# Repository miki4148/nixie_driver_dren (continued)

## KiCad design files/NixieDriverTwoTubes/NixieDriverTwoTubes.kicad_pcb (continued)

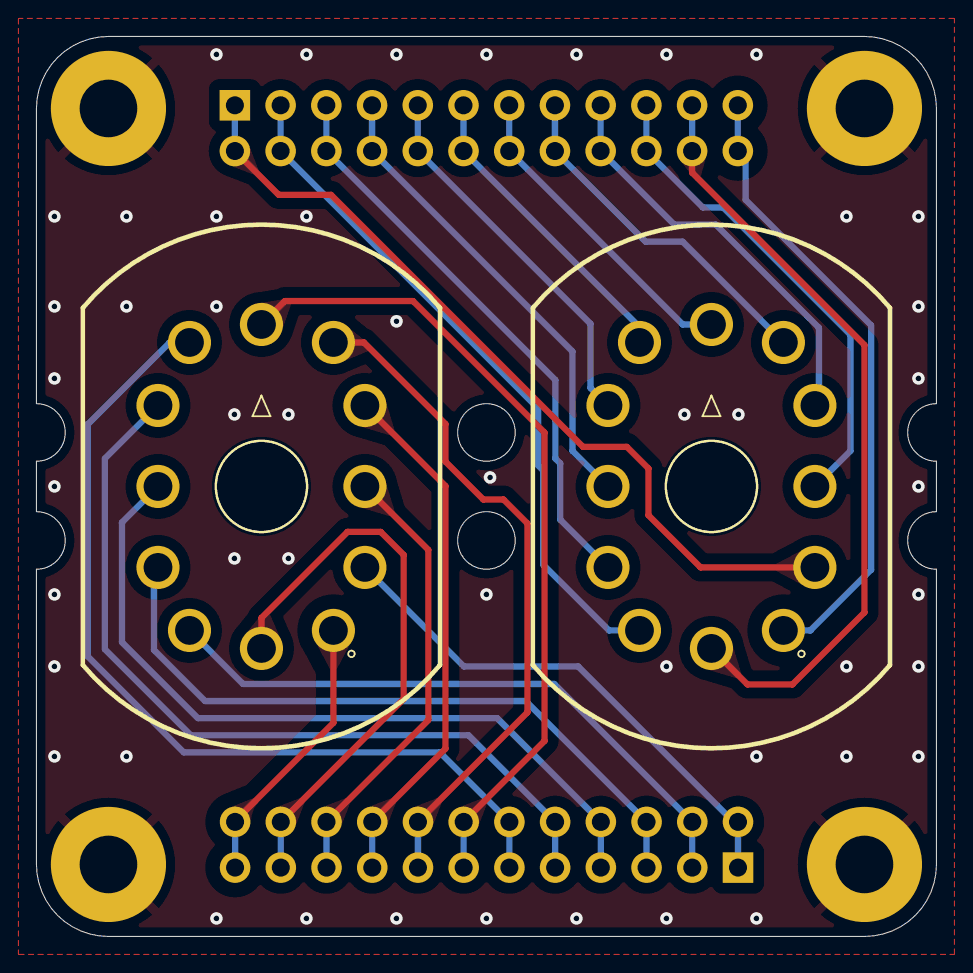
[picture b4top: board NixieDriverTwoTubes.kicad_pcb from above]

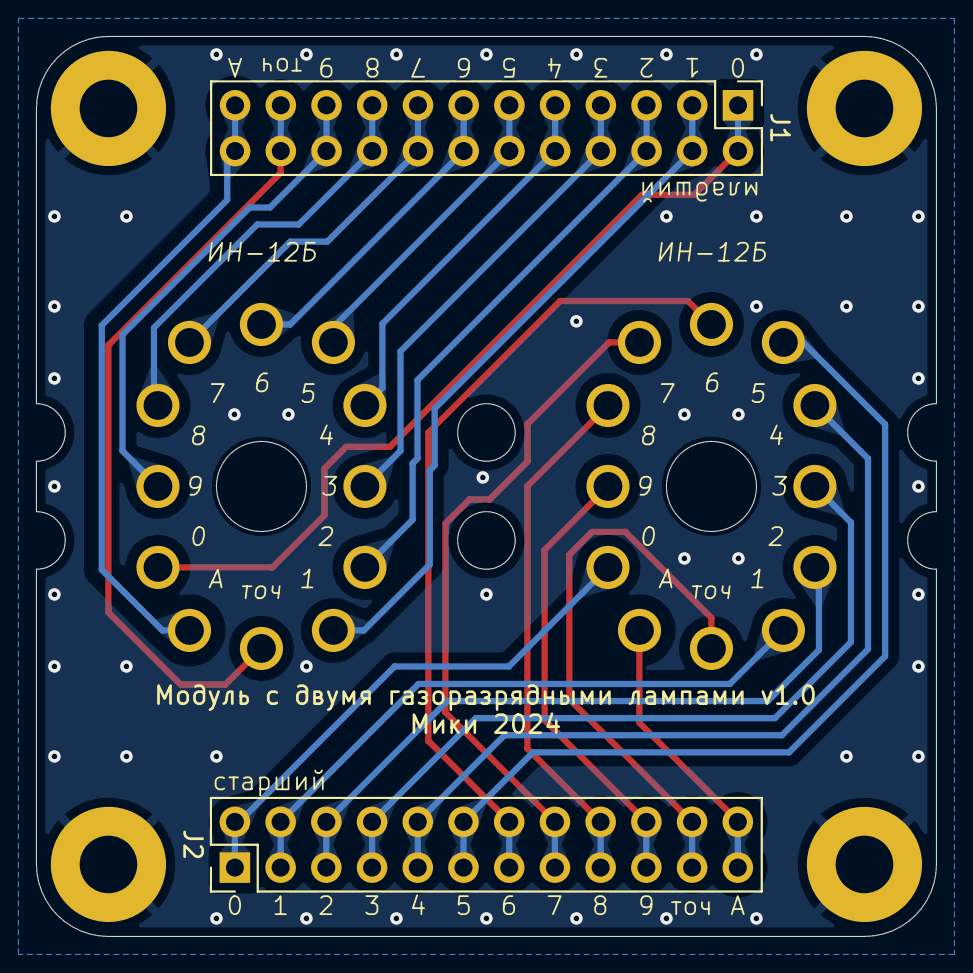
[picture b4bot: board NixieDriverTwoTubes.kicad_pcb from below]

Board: 2 copper layers, 50.0 x 50.0 mm, 8 parts (2 on the bottom side), 25 nets.

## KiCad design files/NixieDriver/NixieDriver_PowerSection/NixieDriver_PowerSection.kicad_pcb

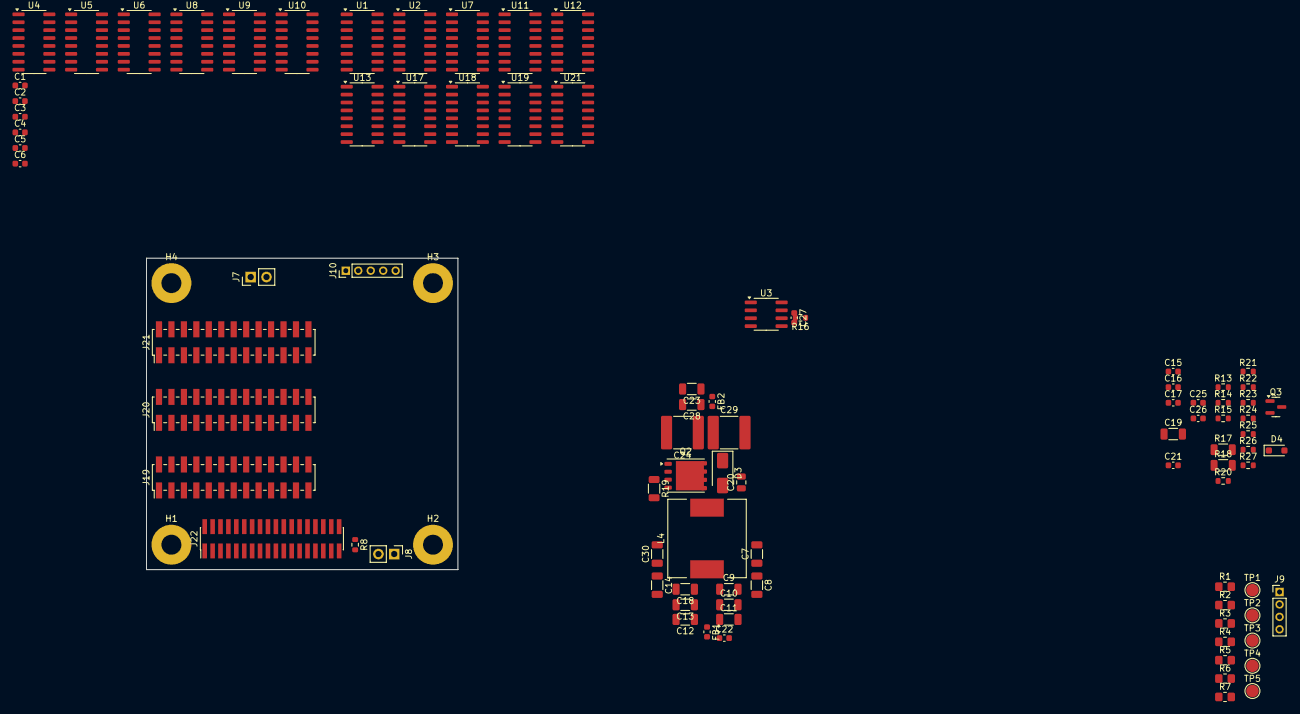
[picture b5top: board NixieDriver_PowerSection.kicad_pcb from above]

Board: 8 copper layers, 50.0 x 50.0 mm, 94 parts (0 on the bottom side), 192 nets, no tracks yet.

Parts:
C1, C2, C3, C4, C5, C6, C15, C22, C27: 100n; C_0603_1608Metric
C7, C8, C9, C10, C11, C12, C13, C14, C18, C30: 10u 50V; C_1206_3216Metric
C16: 330p; C_0603_1608Metric
C17: 1n; C_0603_1608Metric
C19: 100p 250V; C_1206_3216Metric
C20: 560p 250V; C_0805_2012Metric
C21: 100u; C_0603_1608Metric
C23, C28: 100n 250V; C_1206_3216Metric
C24, C29: 1u 250V; C_2220_5750Metric
C25: 220p; C_0603_1608Metric
C26: 47u; C_0603_1608Metric
D3: ES1D; D_SMA
D4: BAT54WS-TP; D_SOD-323_HandSoldering
FB1, FB2: 60R@100MHz; L_0603_1608Metric
H1, H2, H3, H4: MountingHole_Pad; MountingHole_3.2mm_M3_Pad
J7: B+_OUT; PinHeader_1x02_P2.54mm_Vertical
J8: V_IN; PinHeader_1x02_P2.54mm_Vertical
J9: ~{EN}; PinHeader_1x04_P2.00mm_Vertical
J10: Extras; PinHeader_1x05_P2.00mm_Vertical
J19: TubesAB; PinHeader_2x13_P2.00mm_Vertical_SMD
J20: TubesCD; PinHeader_2x13_P2.00mm_Vertical_SMD
J21: TubesEF; PinHeader_2x13_P2.00mm_Vertical_SMD
J22: BCD_IN; PinHeader_2x18_P1.27mm_Vertical_SMD
L4: 330u; L_12x12mm_H8mm
Q2: BSC900N20NS3 G; Infineon_PG-TDSON-8_6.15x5.15mm
Q3: MMBTA42; SOT-23
R1, R2, R3, R4, R5, R6, R7: 8.66k; R_0805_2012Metric_Pad1.20x1.40mm_HandSolder
R8, R20, R21, R26: 0; R_0603_1608Metric
R13: 41.2k; R_0603_1608Metric
R14: 4.12k; R_0603_1608Metric
R15, R25: 1k; R_0603_1608Metric
R16: 10R; R_0603_1608Metric
R17: 634k, 1%; R_1206_3216Metric
R18: 7.68k, 1%; R_1206_3216Metric
R19: 0R1, 1/2W; R_1206_3216Metric
R22: 2k; R_0603_1608Metric
R23, R24: 100k; R_0603_1608Metric
R27: 24R; R_0603_1608Metric
TP1: TP_FB; TestPoint_Pad_D2.0mm
TP2: TP_GATE; TestPoint_Pad_D2.0mm
TP3: TP_COMP; TestPoint_Pad_D2.0mm
TP4: TP_ISENSE; TestPoint_Pad_D2.0mm
TP5: TP_GND; TestPoint_Pad_D2.0mm
U1, U2, U7, U11, U12, U13, U17, U18, U19, U21: SN75468; SOIC-16_3.9x9.9mm_P1.27mm
U3: UCC3800; SOIC-8_3.9x4.9mm_P1.27mm
U4, U5, U6, U8, U9, U10: 4028; SOIC-16_3.9x9.9mm_P1.27mm

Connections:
/A11: J22.26, U2.4 (I4)
/A_bit0: J22.1, U5.10 (A)
/A_bit1: J22.3, U5.13 (B)
/A_bit2: J22.5, U5.12 (C)
/A_bit3: J22.7, U5.11 (D)
/B11: J22.28, U11.1 (I1)
/B_bit0: J22.9, U4.10 (A)
/B_bit1: J22.11, U4.13 (B)
/B_bit2: J22.13, U4.12 (C)
/B_bit3: J22.15, U4.11 (D)
/C11: J22.30, U12.5 (I5)
/C_bit0: J22.17, U6.10 (A)
/C_bit1: J22.19, U6.13 (B)
/C_bit2: J22.21, U6.12 (C)
/C_bit3: J22.23, U6.11 (D)
/D11: J22.32, U17.2 (I2)
/D_bit0: J22.25, U8.10 (A)
/D_bit1: J22.27, U8.13 (B)
/D_bit2: J22.29, U8.12 (C)
/D_bit3: J22.31, U8.11 (D)
/DemultiplexerArray/A01: U1.1 (I1), U5.3 (S0)
/DemultiplexerArray/A02: U1.2 (I2), U5.14 (S1)
/DemultiplexerArray/A03: U1.3 (I3), U5.2 (S2)
/DemultiplexerArray/A04: U1.4 (I4), U5.15 (S3)
/DemultiplexerArray/A05: U1.5 (I5), U5.1 (S4)
/DemultiplexerArray/A06: U1.6 (I6), U5.6 (S5)
/DemultiplexerArray/A07: U1.7 (I7), U5.7 (S6)
/DemultiplexerArray/A08: U2.1 (I1), U5.4 (S7)
/DemultiplexerArray/A09: U2.2 (I2), U5.9 (S8)
/DemultiplexerArray/A10: U2.3 (I3), U5.5 (S9)
/DemultiplexerArray/B01: U2.5 (I5), U4.3 (S0)
/DemultiplexerArray/B02: U2.6 (I6), U4.14 (S1)
/DemultiplexerArray/B03: U2.7 (I7), U4.2 (S2)
/DemultiplexerArray/B04: U4.15 (S3), U7.1 (I1)
/DemultiplexerArray/B05: U4.1 (S4), U7.2 (I2)
/DemultiplexerArray/B06: U4.6 (S5), U7.3 (I3)
/DemultiplexerArray/B07: U4.7 (S6), U7.4 (I4)
/DemultiplexerArray/B08: U4.4 (S7), U7.5 (I5)
/DemultiplexerArray/B09: U4.9 (S8), U7.6 (I6)
/DemultiplexerArray/B10: U4.5 (S9), U7.7 (I7)
/DemultiplexerArray/C01: U6.3 (S0), U11.2 (I2)
/DemultiplexerArray/C02: U6.14 (S1), U11.3 (I3)
/DemultiplexerArray/C03: U6.2 (S2), U11.4 (I4)
/DemultiplexerArray/C04: U6.15 (S3), U11.5 (I5)
/DemultiplexerArray/C05: U6.1 (S4), U11.6 (I6)
/DemultiplexerArray/C06: U6.6 (S5), U11.7 (I7)
/DemultiplexerArray/C07: U6.7 (S6), U12.1 (I1)
/DemultiplexerArray/C08: U6.4 (S7), U12.2 (I2)
/DemultiplexerArray/C09: U6.9 (S8), U12.3 (I3)
/DemultiplexerArray/C10: U6.5 (S9), U12.4 (I4)
/DemultiplexerArray/D01: U8.3 (S0), U12.6 (I6)
/DemultiplexerArray/D02: U8.14 (S1), U12.7 (I7)
/DemultiplexerArray/D03: U8.2 (S2), U13.1 (I1)
/DemultiplexerArray/D04: U8.15 (S3), U13.2 (I2)
/DemultiplexerArray/D05: U8.1 (S4), U13.3 (I3)
/DemultiplexerArray/D06: U8.6 (S5), U13.4 (I4)
/DemultiplexerArray/D07: U8.7 (S6), U13.5 (I5)
/DemultiplexerArray/D08: U8.4 (S7), U13.6 (I6)
/DemultiplexerArray/D09: U8.9 (S8), U13.7 (I7)
/DemultiplexerArray/D10: U8.5 (S9), U17.1 (I1)
/DemultiplexerArray/E01: U9.3 (S0), U17.3 (I3)
/DemultiplexerArray/E02: U9.14 (S1), U17.4 (I4)
/DemultiplexerArray/E03: U9.2 (S2), U17.5 (I5)
/DemultiplexerArray/E04: U9.15 (S3), U17.6 (I6)
/DemultiplexerArray/E05: U9.1 (S4), U17.7 (I7)
/DemultiplexerArray/E06: U9.6 (S5), U18.1 (I1)
/DemultiplexerArray/E07: U9.7 (S6), U18.2 (I2)
/DemultiplexerArray/E08: U9.4 (S7), U18.3 (I3)
/DemultiplexerArray/E09: U9.9 (S8), U18.4 (I4)
/DemultiplexerArray/E10: U9.5 (S9), U18.5 (I5)
/DemultiplexerArray/F01: U10.3 (S0), U18.7 (I7)
/DemultiplexerArray/F02: U10.14 (S1), U19.1 (I1)
/DemultiplexerArray/F03: U10.2 (S2), U19.2 (I2)
/DemultiplexerArray/F04: U10.15 (S3), U19.3 (I3)
/DemultiplexerArray/F05: U10.1 (S4), U19.4 (I4)
/DemultiplexerArray/F06: U10.6 (S5), U19.5 (I5)
/DemultiplexerArray/F07: U10.7 (S6), U19.6 (I6)
/DemultiplexerArray/F08: U10.4 (S7), U19.7 (I7)
/DemultiplexerArray/F09: U10.9 (S8), U21.1 (I1)
/DemultiplexerArray/F10: U10.5 (S9), U21.2 (I2)
/E11: J22.34, U18.6 (I6)
/E_bit0: J22.10, U9.10 (A)
/E_bit1: J22.12, U9.13 (B)
/E_bit2: J22.14, U9.12 (C)
/E_bit3: J22.16, U9.11 (D)
/F11: J22.36, U21.3 (I3)
/FB: C19.2, R17.1, R18.2, R20.1, R21.1, TP1.1, U3.2 (FB)
/F_bit0: J22.2, U10.10 (A)
/F_bit1: J22.4, U10.13 (B)
/F_bit2: J22.6, U10.12 (C)
/F_bit3: J22.8, U10.11 (D)
/GATE_SIG: R16.2, TP2.1, U3.6 (OUT)
/ISENSE: Q2.1 (S), Q2.2 (S), Q2.3 (S), R15.1, R19.1, TP4.1
/OutTransistorArray/Cath_A01: J19.1, U1.16 (O1)
/OutTransistorArray/Cath_A02: J19.3, U1.15 (O2)
/OutTransistorArray/Cath_A03: J19.5, U1.14 (O3)
/OutTransistorArray/Cath_A04: J19.7, U1.13 (O4)
/OutTransistorArray/Cath_A05: J19.9, U1.12 (O5)
/OutTransistorArray/Cath_A06: J19.11, U1.11 (O6)
/OutTransistorArray/Cath_A07: J19.13, U1.10 (O7)
/OutTransistorArray/Cath_A08: J19.15, U2.16 (O1)
/OutTransistorArray/Cath_A09: J19.17, U2.15 (O2)
/OutTransistorArray/Cath_A10: J19.19, U2.14 (O3)
/OutTransistorArray/Cath_A11: J19.21, U2.13 (O4)
/OutTransistorArray/Cath_B01: J19.2, U2.12 (O5)
/OutTransistorArray/Cath_B02: J19.4, U2.11 (O6)
/OutTransistorArray/Cath_B03: J19.6, U2.10 (O7)
/OutTransistorArray/Cath_B04: J19.8, U7.16 (O1)
/OutTransistorArray/Cath_B05: J19.10, U7.15 (O2)
/OutTransistorArray/Cath_B06: J19.12, U7.14 (O3)
/OutTransistorArray/Cath_B07: J19.14, U7.13 (O4)
/OutTransistorArray/Cath_B08: J19.16, U7.12 (O5)
/OutTransistorArray/Cath_B09: J19.18, U7.11 (O6)
/OutTransistorArray/Cath_B10: J19.20, U7.10 (O7)
/OutTransistorArray/Cath_B11: J19.22, U11.16 (O1)
/OutTransistorArray/Cath_C01: J20.1, U11.15 (O2)
/OutTransistorArray/Cath_C02: J20.3, U11.14 (O3)
/OutTransistorArray/Cath_C03: J20.5, U11.13 (O4)
/OutTransistorArray/Cath_C04: J20.7, U11.12 (O5)
/OutTransistorArray/Cath_C05: J20.9, U11.11 (O6)
/OutTransistorArray/Cath_C06: J20.11, U11.10 (O7)
/OutTransistorArray/Cath_C07: J20.13, U12.16 (O1)
/OutTransistorArray/Cath_C08: J20.15, U12.15 (O2)
/OutTransistorArray/Cath_C09: J20.17, U12.14 (O3)
/OutTransistorArray/Cath_C10: J20.19, U12.13 (O4)
/OutTransistorArray/Cath_C11: J20.21, U12.12 (O5)
/OutTransistorArray/Cath_D01: J20.2, U12.11 (O6)
/OutTransistorArray/Cath_D02: J20.4, U12.10 (O7)
/OutTransistorArray/Cath_D03: J20.6, U13.16 (O1)
/OutTransistorArray/Cath_D04: J20.8, U13.15 (O2)
/OutTransistorArray/Cath_D05: J20.10, U13.14 (O3)
/OutTransistorArray/Cath_D06: J20.12, U13.13 (O4)
/OutTransistorArray/Cath_D07: J20.14, U13.12 (O5)
/OutTransistorArray/Cath_D08: J20.16, U13.11 (O6)
/OutTransistorArray/Cath_D09: J20.18, U13.10 (O7)
/OutTransistorArray/Cath_D10: J20.20, U17.16 (O1)
/OutTransistorArray/Cath_D11: J20.22, U17.15 (O2)
/OutTransistorArray/Cath_E01: J21.1, U17.14 (O3)
/OutTransistorArray/Cath_E02: J21.3, U17.13 (O4)
/OutTransistorArray/Cath_E03: J21.5, U17.12 (O5)
/OutTransistorArray/Cath_E04: J21.7, U17.11 (O6)
/OutTransistorArray/Cath_E05: J21.9, U17.10 (O7)
/OutTransistorArray/Cath_E06: J21.11, U18.16 (O1)
/OutTransistorArray/Cath_E07: J21.13, U18.15 (O2)
/OutTransistorArray/Cath_E08: J21.15, U18.14 (O3)
/OutTransistorArray/Cath_E09: J21.17, U18.13 (O4)
/OutTransistorArray/Cath_E10: J21.19, U18.12 (O5)
/OutTransistorArray/Cath_E11: J21.21, U18.11 (O6)
/OutTransistorArray/Cath_F01: J21.2, U18.10 (O7)
/OutTransistorArray/Cath_F02: J21.4, U19.16 (O1)
/OutTransistorArray/Cath_F03: J21.6, U19.15 (O2)
/OutTransistorArray/Cath_F04: J21.8, U19.14 (O3)
/OutTransistorArray/Cath_F05: J21.10, U19.13 (O4)
/OutTransistorArray/Cath_F06: J21.12, U19.12 (O5)
/OutTransistorArray/Cath_F07: J21.14, U19.11 (O6)
/OutTransistorArray/Cath_F08: J21.16, U19.10 (O7)
/OutTransistorArray/Cath_F09: J21.18, U21.16 (O1)
/OutTransistorArray/Cath_F10: J21.20, U21.15 (O2)
/OutTransistorArray/Cath_F11: J21.22, U21.14 (O3)
/OutTransistorArray/Cath_X01: J10.1, U21.13 (O4)
/OutTransistorArray/Cath_X02: J10.2, U21.12 (O5)
/OutTransistorArray/Cath_X03: J10.3, U21.11 (O6)
/OutTransistorArray/Cath_X04: J10.4, U21.10 (O7)
/X01: J22.18, U21.4 (I4)
/X02: J22.20, U21.5 (I5)
/X03: J22.22, U21.6 (I6)
/X04: J22.24, U21.7 (I7)
/~ENABLE: J9.2, R25.2
B+: C23.1, FB2.1, J7.2, R1.1, R2.1, R3.1, R4.1, R5.1, R6.1, R7.1
GND: C1.2, C2.2, C3.2, C4.2, C5.2, C6.2, C7.2, C8.2, C9.2, C10.2, C11.2, C12.2, C13.2, C14.2, C15.2, C16.2, C17.2, C18.2, C20.2, C21.2, C22.2, C23.2, C24.2, C26.2, C27.2, C28.2, C29.2, C30.2, H1.1, H2.1, H3.1, H4.1, J7.1, J8.1, J9.1, J22.35, Q3.2 (E), R18.1, R19.2, R23.1, TP5.1, U1.8 (GND), U2.8 (GND), U3.5 (GND), U4.8 (VSS), U5.8 (VSS), U6.8 (VSS), U7.8 (GND), U8.8 (VSS), U9.8 (VSS), U10.8 (VSS), U11.8 (GND), U12.8 (GND), U13.8 (GND), U17.8 (GND), U18.8 (GND), U19.8 (GND), U21.8 (GND)
unnamed: C25.2, R20.2
unnamed: C20.1, D3.2 (A), L4.2, Q2.5 (D)
unnamed: C19.1, C24.1, C28.1, C29.1, D3.1 (K), FB2.2, R17.2
unnamed: C25.1, D4.2 (A), R21.2, TP3.1, U3.1 (COMP)
unnamed: C26.1, D4.1 (K), R22.1, R23.2, R27.1
unnamed: J10.5, R7.2
unnamed: J19.25, R1.2
unnamed: J19.26, R2.2
unnamed: J20.25, R3.2
unnamed: J20.26, R4.2
unnamed: J21.25, R5.2
unnamed: J21.26, R6.2
unnamed: J22.33, R8.1
unnamed: Q2.4 (G), R16.1
unnamed: Q3.1 (B), R24.1, R25.1
unnamed: Q3.3 (C), R27.2
unnamed: C17.1, R14.1, R15.2, U3.3 (CS)
unnamed: C16.1, R13.1, U3.4 (RC)
unnamed: C27.1, R26.1, U3.7 (VCC)
VCC: C7.1, C8.1, C9.1, C10.1, C11.1, C12.1, C13.1, C14.1, C18.1, C30.1, FB1.1, L4.1, R26.2
VIN: C1.1, C2.1, C3.1, C4.1, C5.1, C6.1, C21.1, C22.1, FB1.2, J8.2, J9.3, R8.2, R22.2, R24.2, U4.16 (VDD), U5.16 (VDD), U6.16 (VDD), U8.16 (VDD), U9.16 (VDD), U10.16 (VDD)
VREF: C15.1, R13.2, R14.2, U3.8 (REF)

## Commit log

2024-12-29 Added first batch of pngs
    Project NixieDriver module and TwoTube module
2024-12-30 Update README.md
    Begin describing design process
2024-12-31 Create img dir
2024-12-31 Move images to img/
2024-12-31 Include KiCad directories
2024-12-31 Added plecs img
2024-12-31 README continued
2024-12-31 README update
2025-01-01 Add NixieDriverTwoTubesSockets
2025-01-01 Img update
2025-01-01 Update simulation commentary
2025-01-01 Osc comment
2025-01-06 Update feedback
2025-01-07 Update BCu
2025-01-07 Reset and reannotate
